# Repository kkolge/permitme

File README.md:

This product was developed during COVID-19 to 
1. Screen a large number of people based on 3 parameters - Temperature, Pulse Rate and SpO2
2. The purpose was to create a funnel where a large number of people can be screened in a short time so that probably infected people could be provided with a better care
3. The system uses this device as an IoT based data collection unit
4. It stored the data on a backend server which can be then checked during the next screening

The hardware system was developed in C, C++ and the web application was developed in PHP. 

Though this system was deployed at 30+ locations, it could not be scaled up due to delay in approvals during COVID. 

Unfortunately the Unit and Integration tests were lost in a system crash and are not part of the repository

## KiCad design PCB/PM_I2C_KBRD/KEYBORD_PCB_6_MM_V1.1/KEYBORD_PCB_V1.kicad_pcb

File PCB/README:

This folder contains KiCad Project for PCB

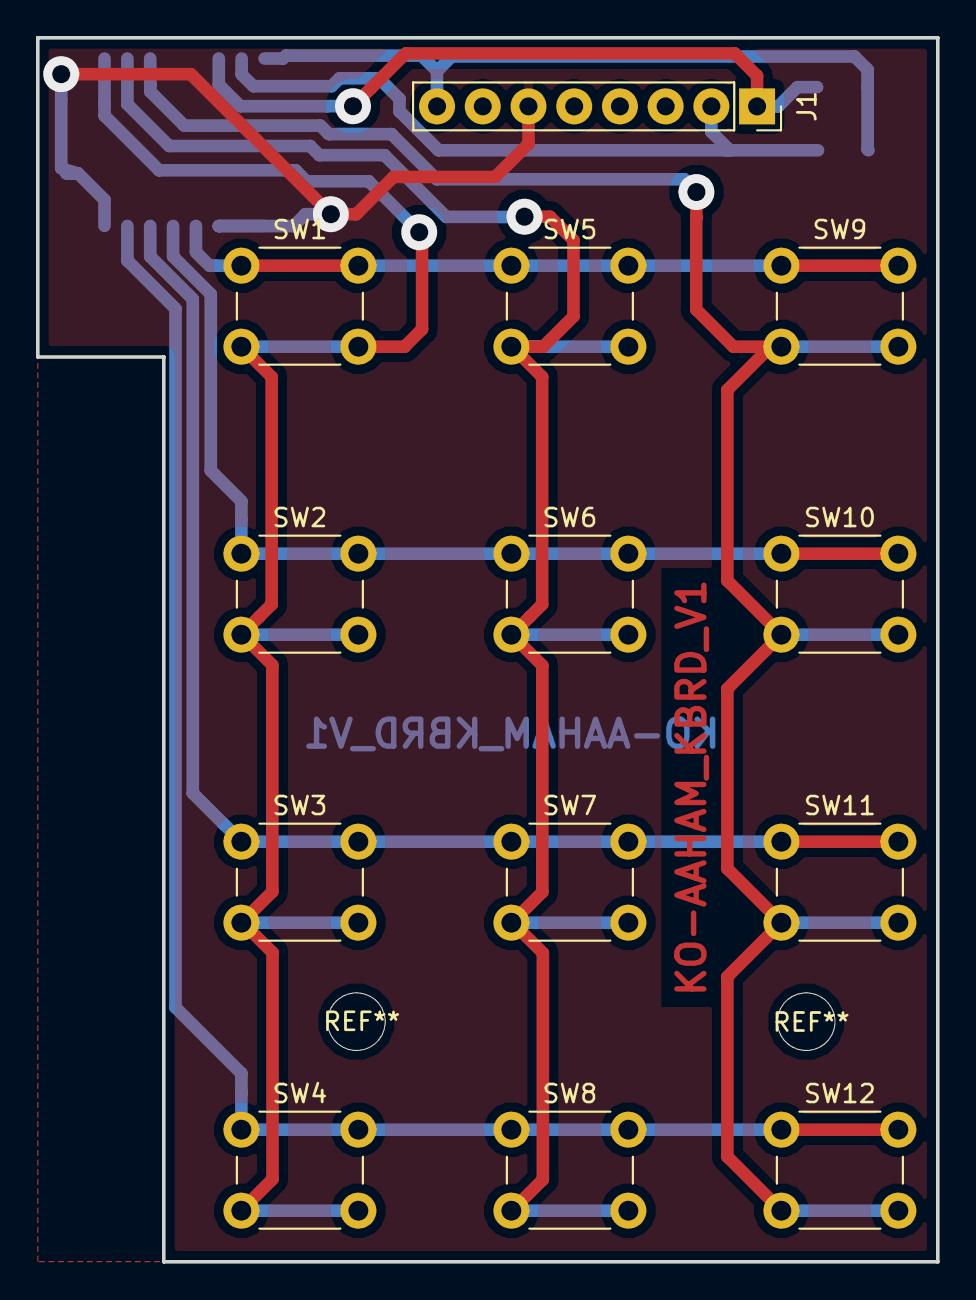
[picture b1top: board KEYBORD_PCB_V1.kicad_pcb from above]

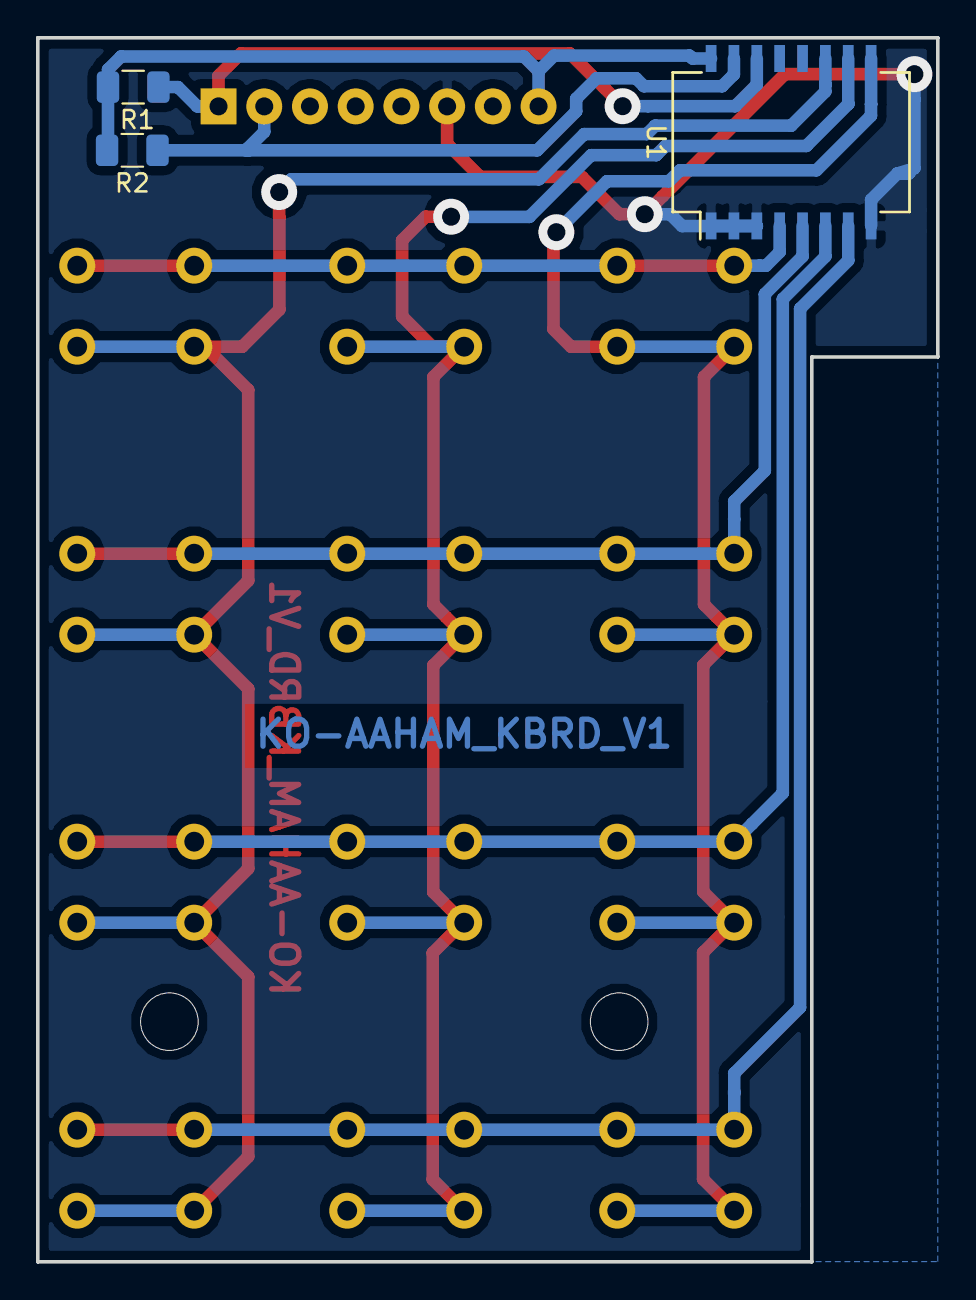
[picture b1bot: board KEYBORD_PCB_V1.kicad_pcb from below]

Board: 2 copper layers, 50.0 x 68.0 mm, 16 parts (3 on the bottom side), 11 nets.

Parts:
J1: Conn_01x08_Male; PinSocket_1x08_P2.54mm_Vertical
R1, R2: 4.7k; R_1206_3216Metric
SW1: 1; SW_PUSH_6mm_H7.3mm
SW2: 4; SW_PUSH_6mm_H7.3mm
SW3: 7; SW_PUSH_6mm_H7.3mm
SW4: CLEAR; SW_PUSH_6mm_H7.3mm
SW5: 2; SW_PUSH_6mm_H7.3mm
SW6: 5; SW_PUSH_6mm_H7.3mm
SW7: 8; SW_PUSH_6mm_H7.3mm
SW8: 0; SW_PUSH_6mm_H7.3mm
SW9: 3; SW_PUSH_6mm_H7.3mm
SW10: 6; SW_PUSH_6mm_H7.3mm
SW11: 9; SW_PUSH_6mm_H7.3mm
SW12: ENTER; SW_PUSH_6mm_H7.3mm
U1: PCF8574; SOIC-16W_7.5x12.8mm_P1.27mm

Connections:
+3V3: J1.8, R1.1, R2.2, U1.16
C1: SW1.2, SW2.2, SW3.2, SW4.2, U1.9
C2: SW5.2, SW6.2, SW7.2, SW8.2, U1.10
C3: SW9.2, SW10.2, SW11.2, SW12.2, U1.11
GND: J1.6, U1.1, U1.2, U1.3, U1.8
R1: SW1.1, SW5.1, SW9.1, U1.4
R2: SW2.1, SW6.1, SW10.1, U1.5
R3: SW3.1, SW7.1, SW11.1, U1.6
R4: SW4.1, SW8.1, SW12.1, U1.7
SCL: J1.1, R1.2, U1.14
SDA: J1.2, R2.1, U1.15

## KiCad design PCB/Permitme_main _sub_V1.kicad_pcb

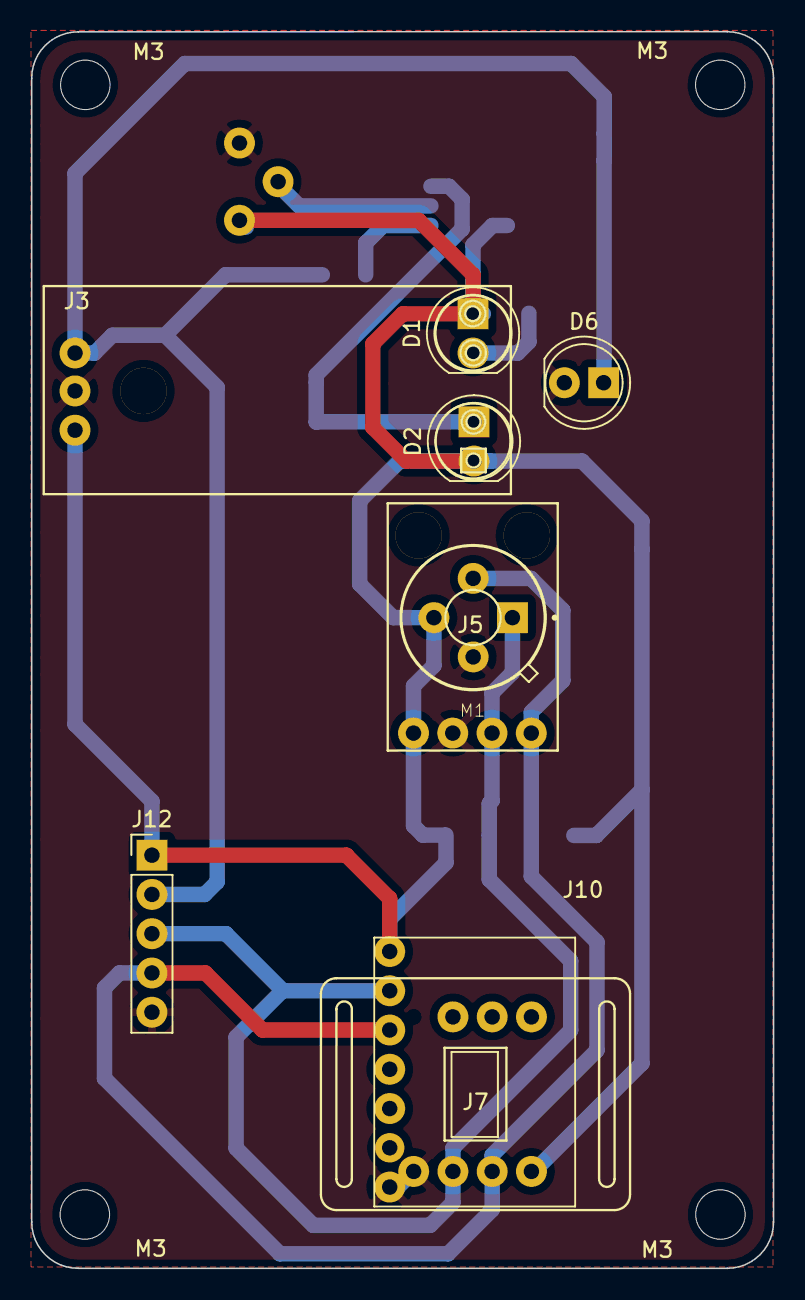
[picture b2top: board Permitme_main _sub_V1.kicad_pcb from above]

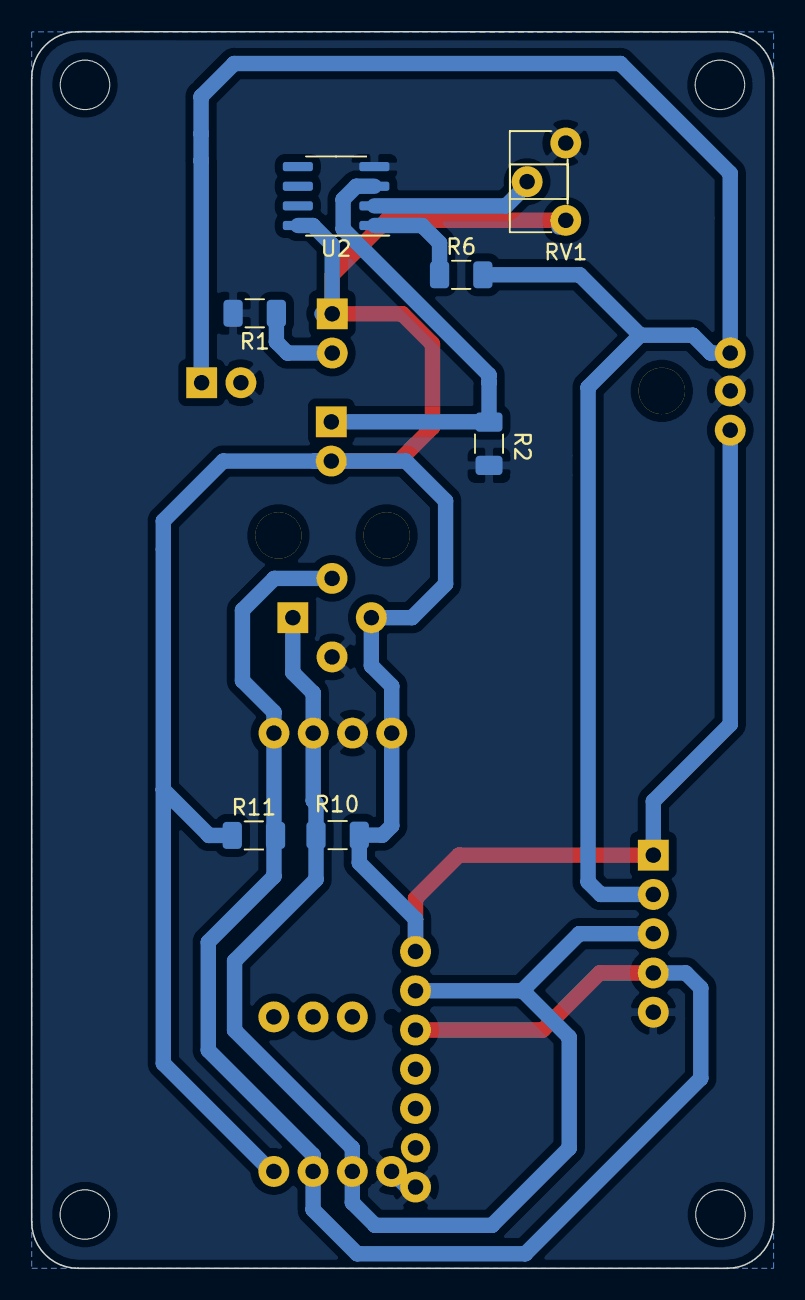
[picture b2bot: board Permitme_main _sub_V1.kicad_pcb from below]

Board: 2 copper layers, 48.0 x 80.0 mm, 20 parts (7 on the bottom side), 9 nets.

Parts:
D1: LED_ALT; LED_D5.0mm
D2: D_Photo_ALT; LED_D5.0mm
D6: LED; LED_D5.0mm
J3: IR Sensor
J5: MLX90614
J7: MAX30102
J10: MAX30102_1
J12: Conn_01x05_Male; PinHeader_1x05_P2.54mm_Vertical
M1: MLX90614ESF-DCA-000-TU; TO254P942H425-4
M3, M3#2, M3#3, M3#4: MountingHole_3.2mm_M3
R1: 100E; R_1206_3216Metric
R2: 10K; R_1206_3216Metric
R6: 330E; R_1206_3216Metric
R10, R11: 220E; R_1206_3216Metric
RV1: 10K; Potentiometer_ACP_CA6-H2,5_Horizontal
U2: LM358; SOIC-8_3.9x4.9mm_P1.27mm

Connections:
+5VA: D1.2, D2.1, J3.3, J5.1, J7.4, J10.1, J12.1, M1.3, R10.1, R11.1, RV1.1, U2.8
GNDA: D6.1, J3.2, J5.2, J7.1, J10.7, J12.5, M1.4, R1.2, R2.2, RV1.3, U2.4
IR1: D6.2, J3.1, J12.2, R6.2
unnamed: D1.1, R1.1
unnamed: D2.2, R2.1, U2.3
unnamed: R6.1, U2.1
unnamed: RV1.2, U2.2
SCL1: J5.3, J7.2, J10.2, J12.3, M1.1, R10.2
SDA1: J5.4, J7.3, J10.3, J12.4, M1.2, R11.2

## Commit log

2020-11-27 Live server backup 27 Nov 2020
2020-11-27 updated README file
2020-11-27 Added folders to store device firmware, Enclosure and PCB
2020-11-27 Added Version 2 of the permit me enclosure
2020-11-27 added local file to store db username and password with extension .temp. DO NOT REPLICATE
2020-11-27 Updated index.php for moving public folder inside
2020-11-27 Hospital dashboard - no Iot data -error fix
2021-01-01 Add all my files
2021-01-02 Adding latest version of enclosure design
2021-01-02 Added enclosure 3p printer files
2021-05-12 v2 database
2021-05-12 New database script
2021-05-15 updated IoT Controller for API
2021-05-15 page alighment issues
2021-05-15 Changes to design
2021-05-18 added test script for iotController and added device type
2021-05-31 V3 - New UI and summary tables
2021-05-31 V3 db script
2021-06-04 V5 combine RFID and Keyboard
    EEPROM DEV ID , Token LCD Storage
2021-06-04 Added stand alone firmware for permitme
2021-06-05 Code review 1
2021-06-15 Permit-Me_V6 OTA UPDATE for RFID & KBRD
2021-06-21 Bill plans and IotDataController
2021-06-21 Added Blank DB and minor changes to handle it
2021-06-21 Changes sequence of response for IotDataController
2021-06-23 Response messages from IoTComreoller
2021-08-05 Bus fixes and billing functionality disabled
2021-08-05 Updated db file for V5
2021-10-07 V7-I2C KPD, V8-DEV Setup serial
2021-11-13 permitmemass_V5.0.sql edited online with Bitbucket based on pmsrv2
2021-11-13 added keypad pcb
